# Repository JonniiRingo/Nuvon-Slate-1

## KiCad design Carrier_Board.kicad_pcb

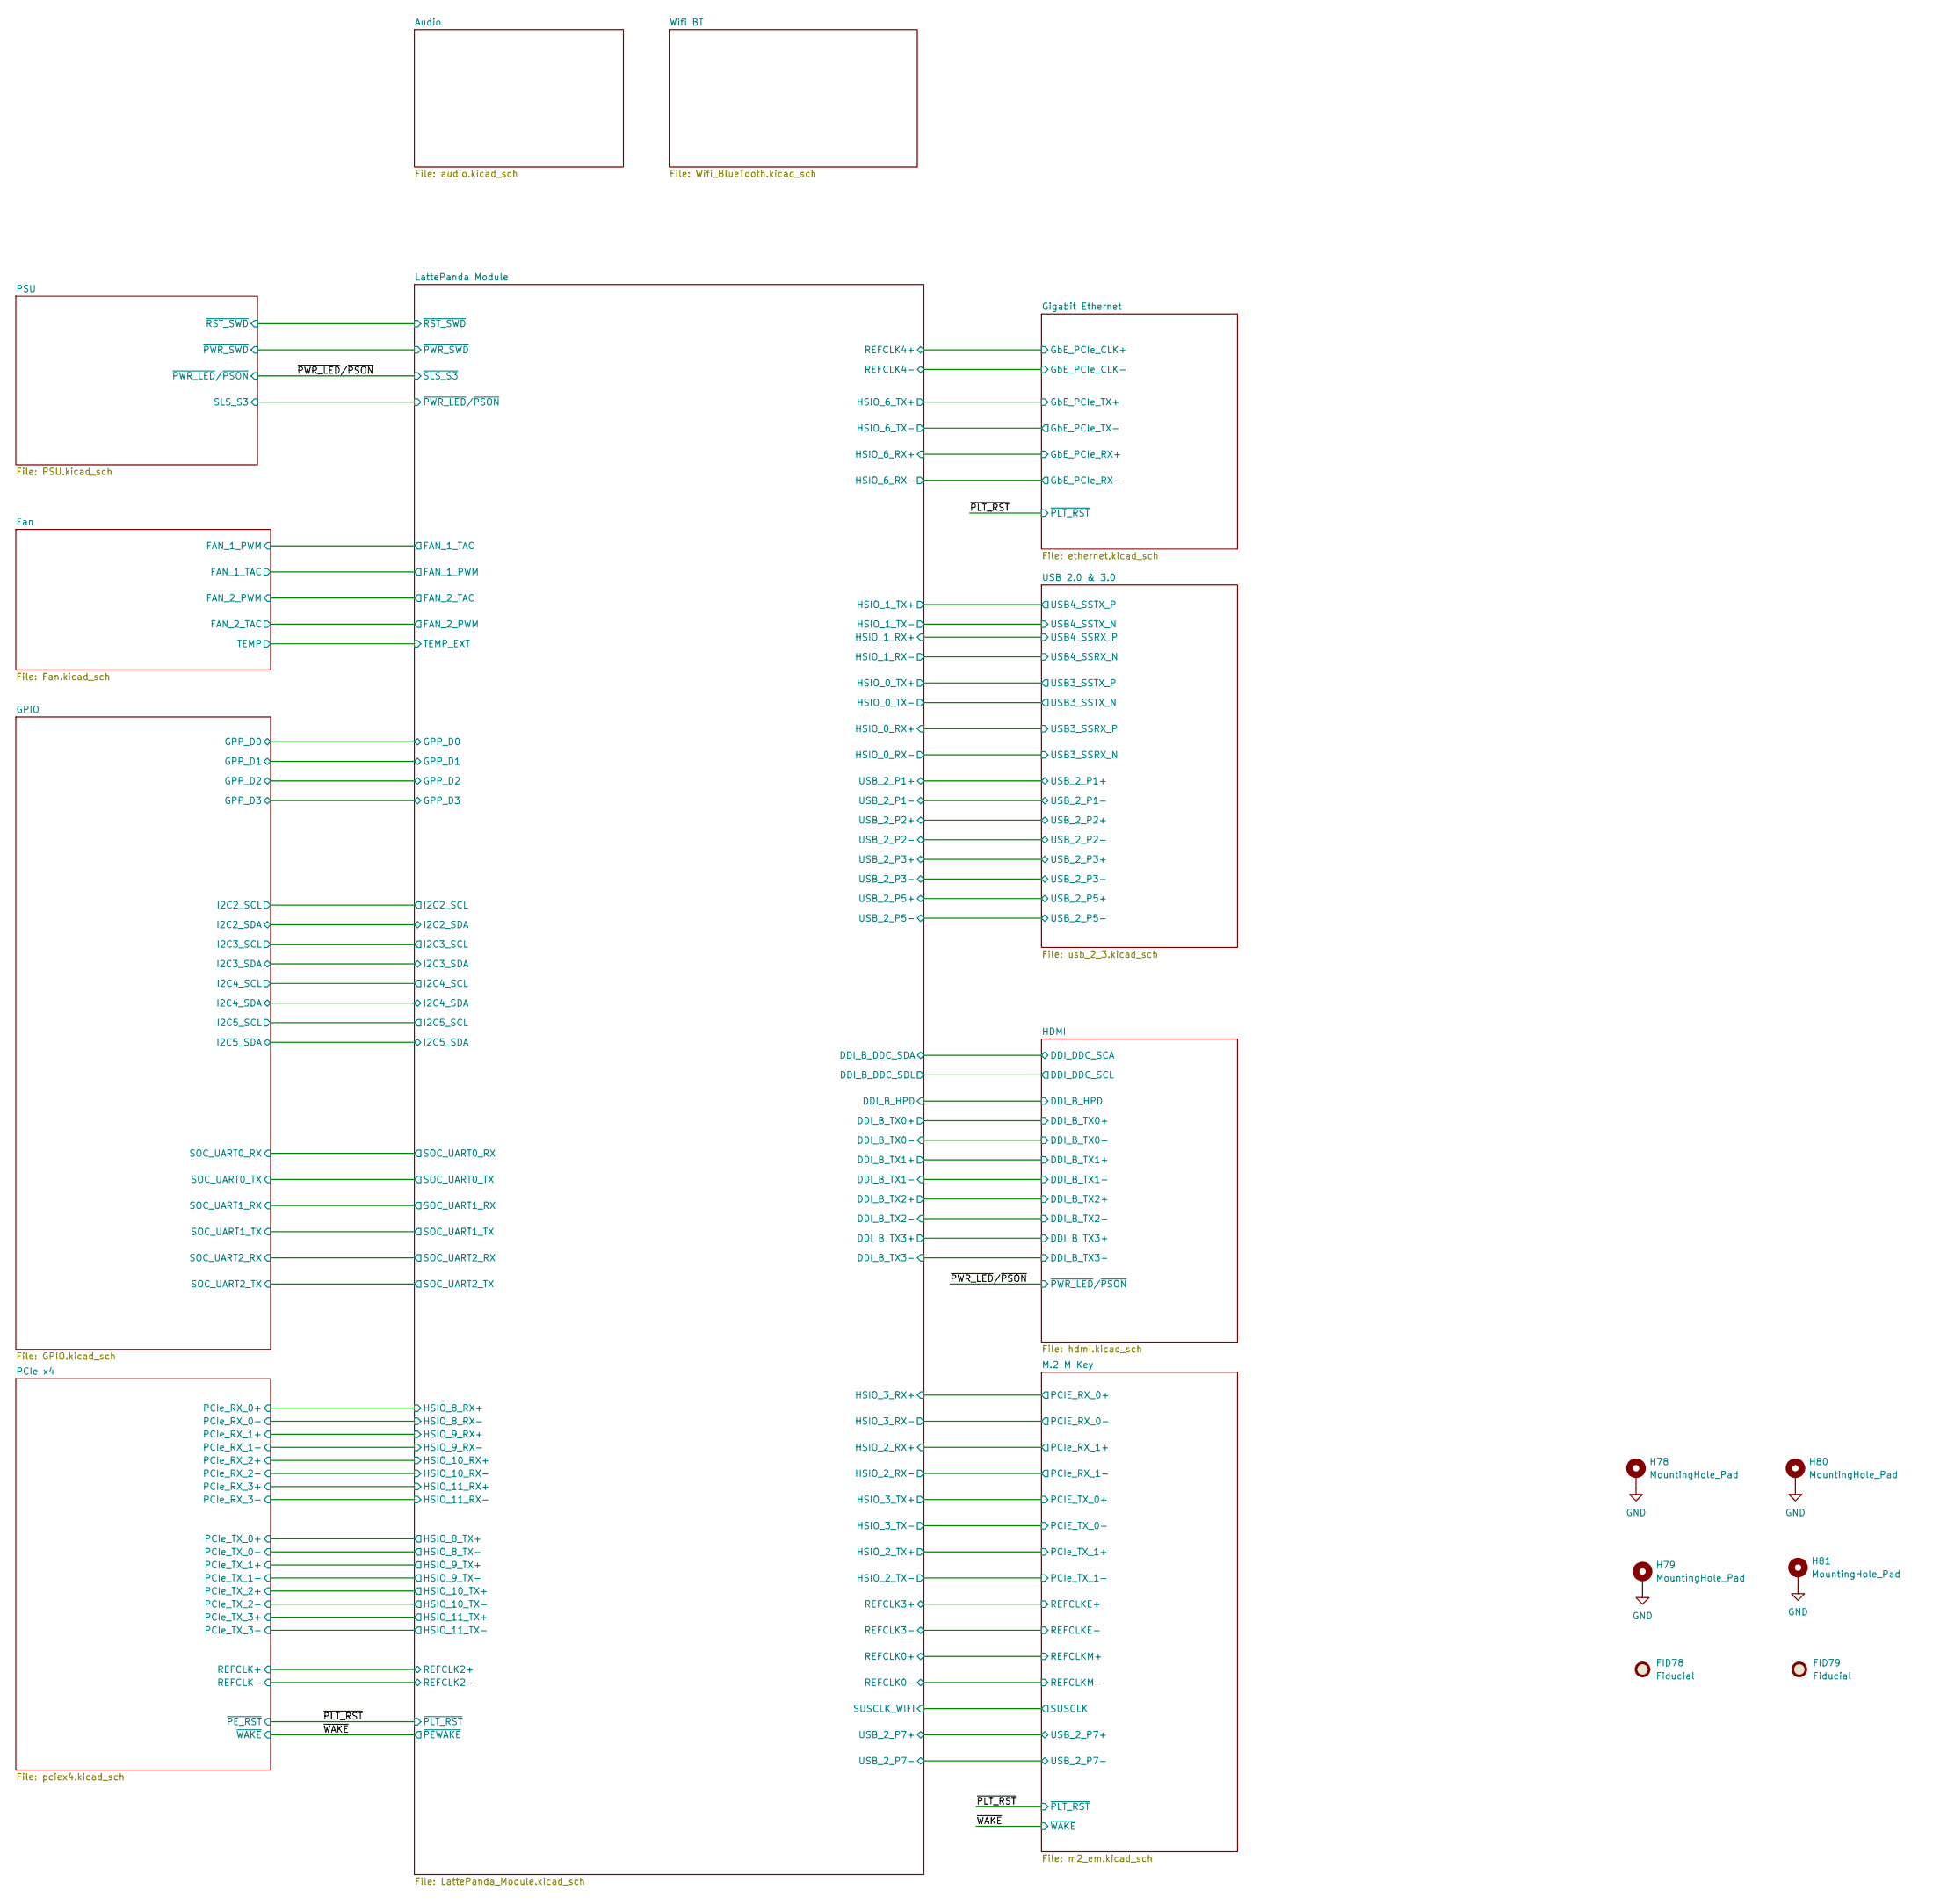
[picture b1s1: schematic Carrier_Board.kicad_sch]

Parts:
FID78, FID79: Fiducial; Fiducial_0.5mm_Mask1mm
H78, H79, H80, H81: MountingHole_Pad; MountingHole_3.2mm_M3_Pad_Via

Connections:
GND: H78.1 (1_1), H79.1 (1_1), H80.1 (1_1), H81.1 (1_1); also elsewhere on the board

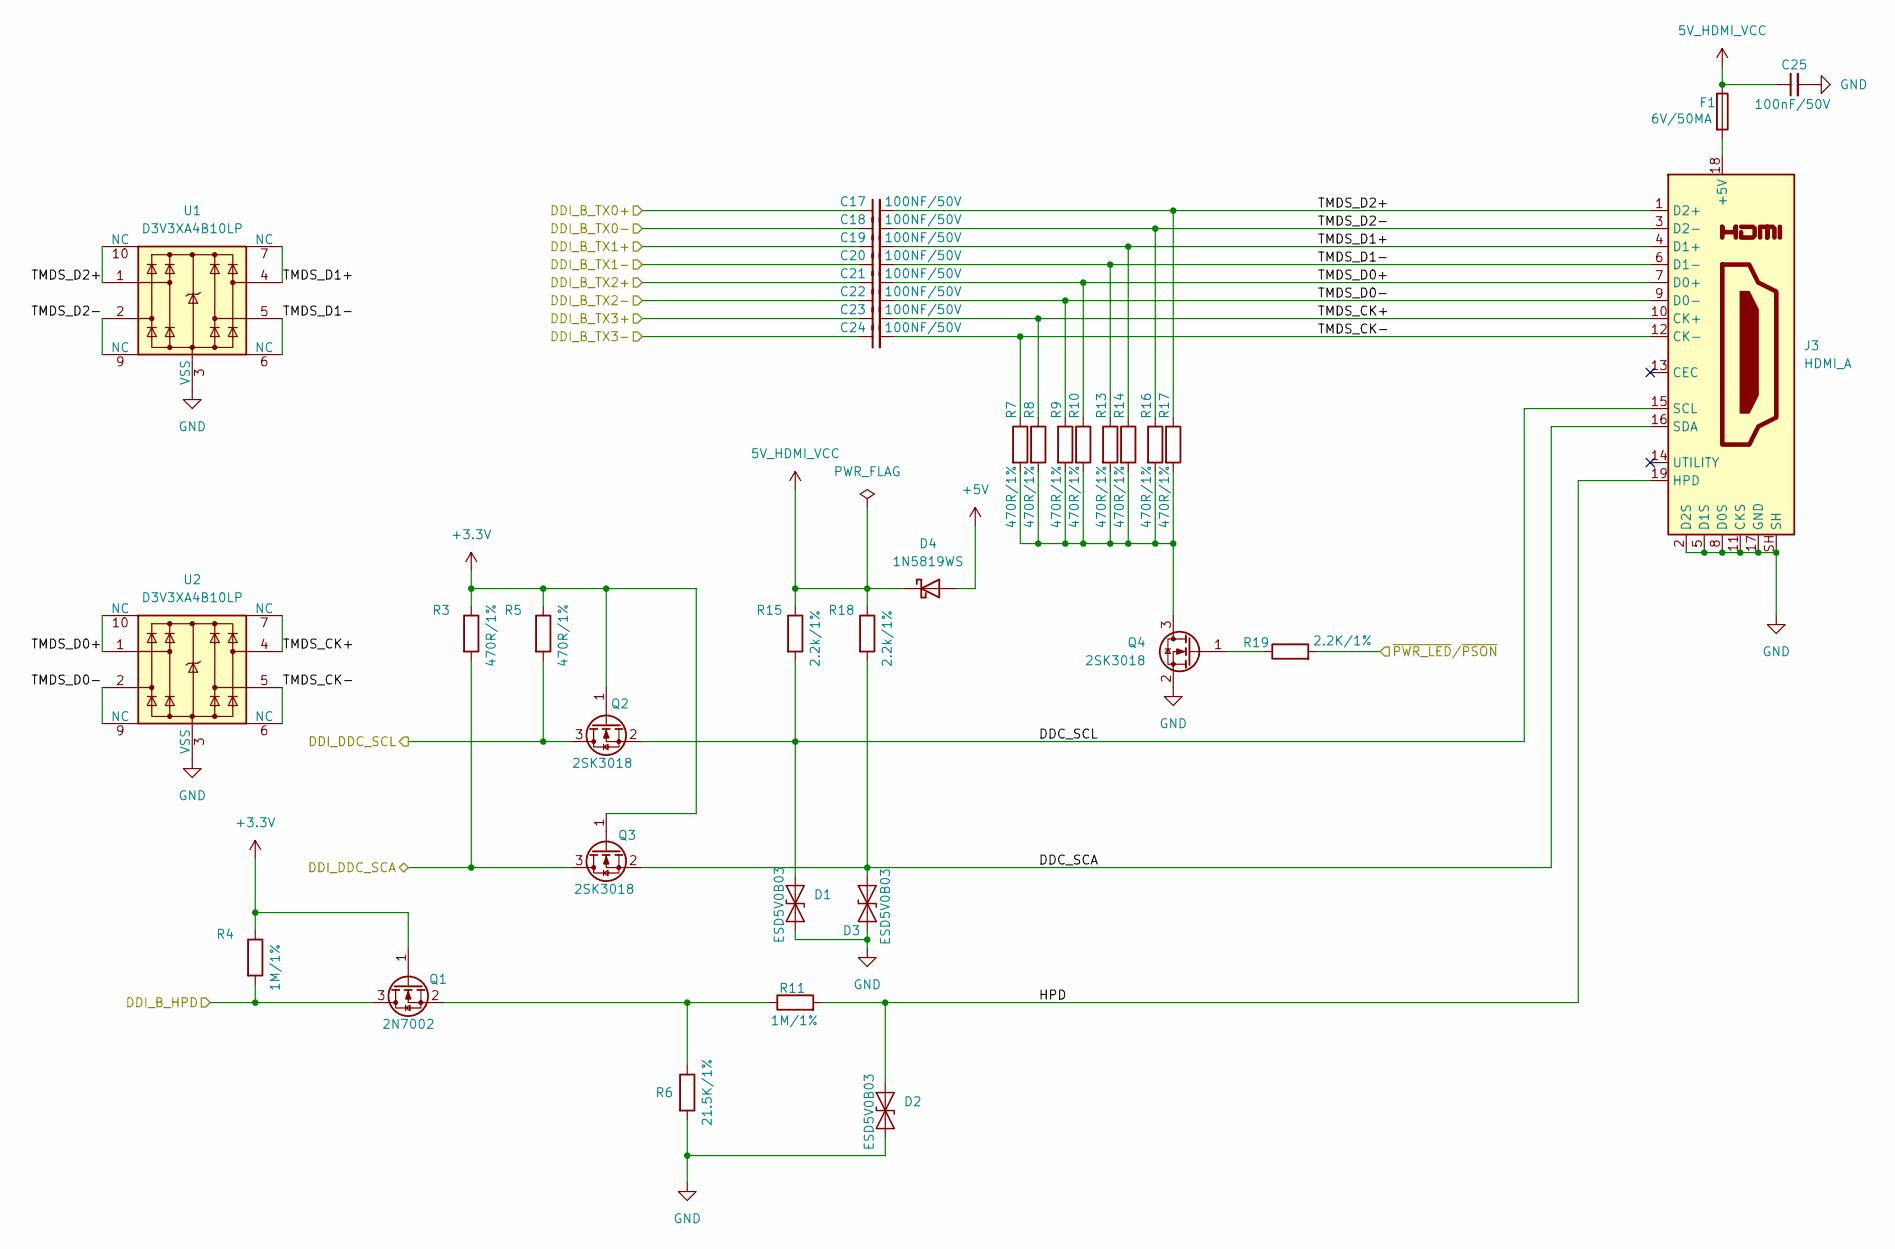
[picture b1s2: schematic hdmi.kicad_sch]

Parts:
C17, C18, C19, C20, C21, C22, C23, C24: 100NF/50V; C_0402_1005Metric
C25: 100nF/50V; C_0402_1005Metric
D1, D2, D3: ESD5V0B03; D_0402_1005Metric
D4: 1N5819WS; D_SOD-323
F1: 6V/50MA; C_0603_1608Metric
J3: HDMI_A; HDMI_A_Molex_208658-1001_Horizontal
Q1: 2N7002; SOT-23
Q2, Q3, Q4: 2SK3018; SOT-23
R3, R5, R7, R8, R9, R10, R13, R14, R16, R17: 470R/1%; R_0402_1005Metric
R4, R11: 1M/1%; R_0402_1005Metric
R6: 21.5K/1%; R_0402_1005Metric
R15, R18: 2.2k/1%; R_0402_1005Metric
R19: 2.2K/1%; R_0402_1005Metric
U1, U2: D3V3XA4B10LP; Diodes_UDFN-10_1.0x2.5mm_P0.5mm

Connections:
5V_HDMI_VCC: C25.1, D4.1 (K), F1.1, R15.1, R18.1
+3.3V: Q1.1 (G), Q2.1 (G), Q3.1 (G), R3.1, R4.1, R5.1; also elsewhere on the board
+5V: D4.2 (A); also elsewhere on the board
/HDMI/DDC_SCA: D3.2 (A2), J3.16 (SDA), Q3.2 (S), R18.2
/HDMI/DDC_SCL: D1.2 (A2), J3.15 (SCL), Q2.2 (S), R15.2
/HDMI/DDI_B_HPD: Q1.3 (D), R4.2; also elsewhere on the board
/HDMI/DDI_B_TX0+: C17.1; also elsewhere on the board
/HDMI/DDI_B_TX0-: C18.1; also elsewhere on the board
/HDMI/DDI_B_TX1+: C19.1; also elsewhere on the board
/HDMI/DDI_B_TX1-: C20.1; also elsewhere on the board
/HDMI/DDI_B_TX2+: C21.1; also elsewhere on the board
/HDMI/DDI_B_TX2-: C22.1; also elsewhere on the board
/HDMI/DDI_B_TX3+: C23.1; also elsewhere on the board
/HDMI/DDI_B_TX3-: C24.1; also elsewhere on the board
/HDMI/DDI_DDC_SCA: Q3.3 (D), R3.2; also elsewhere on the board
/HDMI/DDI_DDC_SCL: Q2.3 (D), R5.2; also elsewhere on the board
/HDMI/HPD: D2.2 (A2), J3.19 (HPD), R11.2
/HDMI/TMDS_CK+: C23.2, J3.10 (CK+), R8.1, U2.4, U2.7 (NC)
/HDMI/TMDS_CK-: C24.2, J3.12 (CK-), R7.1, U2.5, U2.6 (NC)
/HDMI/TMDS_D0+: C21.2, J3.7 (D0+), R10.1, U2.1, U2.10 (NC)
/HDMI/TMDS_D0-: C22.2, J3.9 (D0-), R9.1, U2.2, U2.9 (NC)
/HDMI/TMDS_D1+: C19.2, J3.4 (D1+), R14.1, U1.4, U1.7 (NC)
/HDMI/TMDS_D1-: C20.2, J3.6 (D1-), R13.1, U1.5, U1.6 (NC)
/HDMI/TMDS_D2+: C17.2, J3.1 (D2+), R17.1, U1.1, U1.10 (NC)
/HDMI/TMDS_D2-: C18.2, J3.3 (D2-), R16.1, U1.2, U1.9 (NC)
/~PWR_LED/~PSON: R19.2; also elsewhere on the board
GND: C25.2, D1.1 (A1), D2.1 (A1), D3.1 (A1), J3.2 (D2S), J3.5 (D1S), J3.8 (D0S), J3.11 (CKS), J3.17 (GND), J3.SH, Q4.2 (S), R6.2, U1.3 (VSS), U1.8 (VSS), U2.3 (VSS), U2.8 (VSS); also elsewhere on the board
unnamed: F1.2, J3.18 (+5V)
unnamed: Q1.2 (S), R6.1, R11.1
unnamed: Q4.3 (D), R7.2, R8.2, R9.2, R10.2, R13.2, R14.2, R16.2, R17.2
unnamed: Q4.1 (G), R19.1

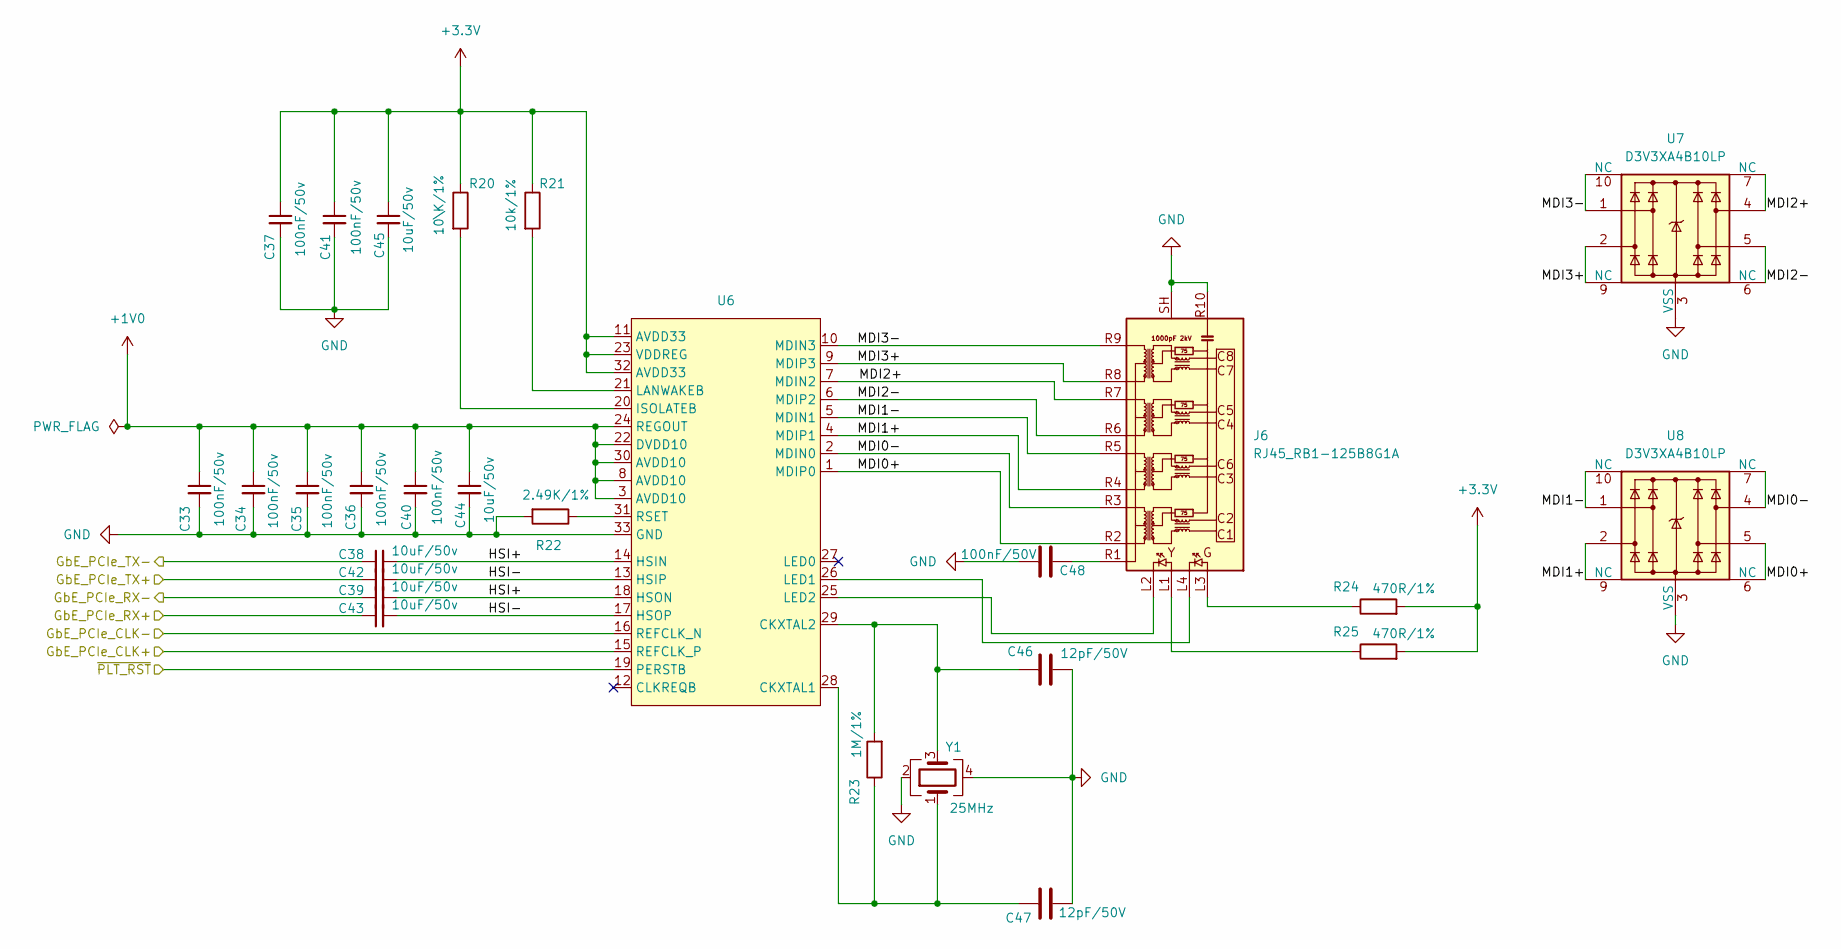
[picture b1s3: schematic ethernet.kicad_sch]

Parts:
C33, C34, C35, C36, C37, C40, C41: 100nF/50v; C_0402_1005Metric
C38, C39, C42, C43, C44, C45: 10uF/50v; C_0402_1005Metric
C46, C47: 12pF/50V; C_0402_1005Metric
C48: 100nF/50V; C_0402_1005Metric
J6: RJ45_RB1-125B8G1A; RJ45_UDE_RB1-125B8G1A
R20: 10\K/1%; R_0603_1608Metric
R21: 10k/1%; R_0603_1608Metric
R22: 2.49K/1%; R_0603_1608Metric
R23: 1M/1%; R_0402_1005Metric
R24, R25: 470R/1%; R_0402_1005Metric
U6: RTL8111H-CG-RH; QFN-32-1EP_4x4mm_P0.4mm_EP2.65x2.65mm
U7, U8: D3V3XA4B10LP; Diodes_UDFN-10_1x2.5mm_P0.5mm
Y1: 25MHz; Crystal_SMD_3225-4Pin_3.2x2.5mm

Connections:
+1V0: C33.1, C34.1, C35.1, C36.1, C40.1, C44.1, U6.3 (AVDD10), U6.8 (AVDD10), U6.22 (DVDD10), U6.24 (REGOUT), U6.30 (AVDD10)
+3.3V: C37.1, C41.1, C45.1, R20.1, R21.1, R24.2, R25.2, U6.11 (AVDD33), U6.23 (VDDREG), U6.32 (AVDD33); also elsewhere on the board
/Gigabit Ethernet/GbE_PCIe_CLK+: U6.15 (REFCLK_P); also elsewhere on the board
/Gigabit Ethernet/GbE_PCIe_CLK-: U6.16 (REFCLK_N); also elsewhere on the board
/Gigabit Ethernet/GbE_PCIe_RX+: C43.1; also elsewhere on the board
/Gigabit Ethernet/GbE_PCIe_RX-: C39.1; also elsewhere on the board
/Gigabit Ethernet/GbE_PCIe_TX+: C42.1; also elsewhere on the board
/Gigabit Ethernet/GbE_PCIe_TX-: C38.1; also elsewhere on the board
/Gigabit Ethernet/HSI+: C38.2, C39.2, U6.14 (HSIN), U6.18 (HSON)
/Gigabit Ethernet/HSI-: C42.2, C43.2, U6.13 (HSIP), U6.17 (HSOP)
/Gigabit Ethernet/MDI0+: J6.R2 (TD1+), U6.1 (MDIP0), U8.5, U8.6 (NC)
/Gigabit Ethernet/MDI0-: J6.R3 (TD1-), U6.2 (MDIN0), U8.4, U8.7 (NC)
/Gigabit Ethernet/MDI1+: J6.R4 (TD2+), U6.4 (MDIP1), U8.2, U8.9 (NC)
/Gigabit Ethernet/MDI1-: J6.R5 (TD2-), U6.5 (MDIN1), U8.1, U8.10 (NC)
/Gigabit Ethernet/MDI2+: J6.R7 (TD3-), U6.7 (MDIN2), U7.4, U7.7 (NC)
/Gigabit Ethernet/MDI2-: J6.R6 (TD3+), U6.6 (MDIP2), U7.5, U7.6 (NC)
/Gigabit Ethernet/MDI3+: J6.R8 (TD4+), U6.9 (MDIP3), U7.2, U7.9 (NC)
/Gigabit Ethernet/MDI3-: J6.R9 (TD4-), U6.10 (MDIN3), U7.1, U7.10 (NC)
/~PLT_RST: U6.19 (PERSTB); also elsewhere on the board
GND: C33.2, C34.2, C35.2, C36.2, C37.2, C40.2, C41.2, C44.2, C45.2, C46.2, C47.2, C48.1, J6.R10 (GND), J6.SH, R22.2, U6.33 (GND), U7.3 (VSS), U7.8 (VSS), U8.3 (VSS), U8.8 (VSS), Y1.2 (G), Y1.4 (G); also elsewhere on the board
unnamed: C48.2, J6.R1 (CT)
unnamed: J6.L1, R25.1
unnamed: J6.L3, R24.1
unnamed: C47.1, R23.1, U6.28 (CKXTAL1), Y1.1
unnamed: C46.1, R23.2, U6.29 (CKXTAL2), Y1.3
unnamed: R20.2, U6.20 (ISOLATEB)
unnamed: R21.2, U6.21 (LANWAKEB)
unnamed: J6.L4, U6.26 (LED1)
unnamed: J6.L2, U6.25 (LED2)
unnamed: R22.1, U6.31 (RSET)

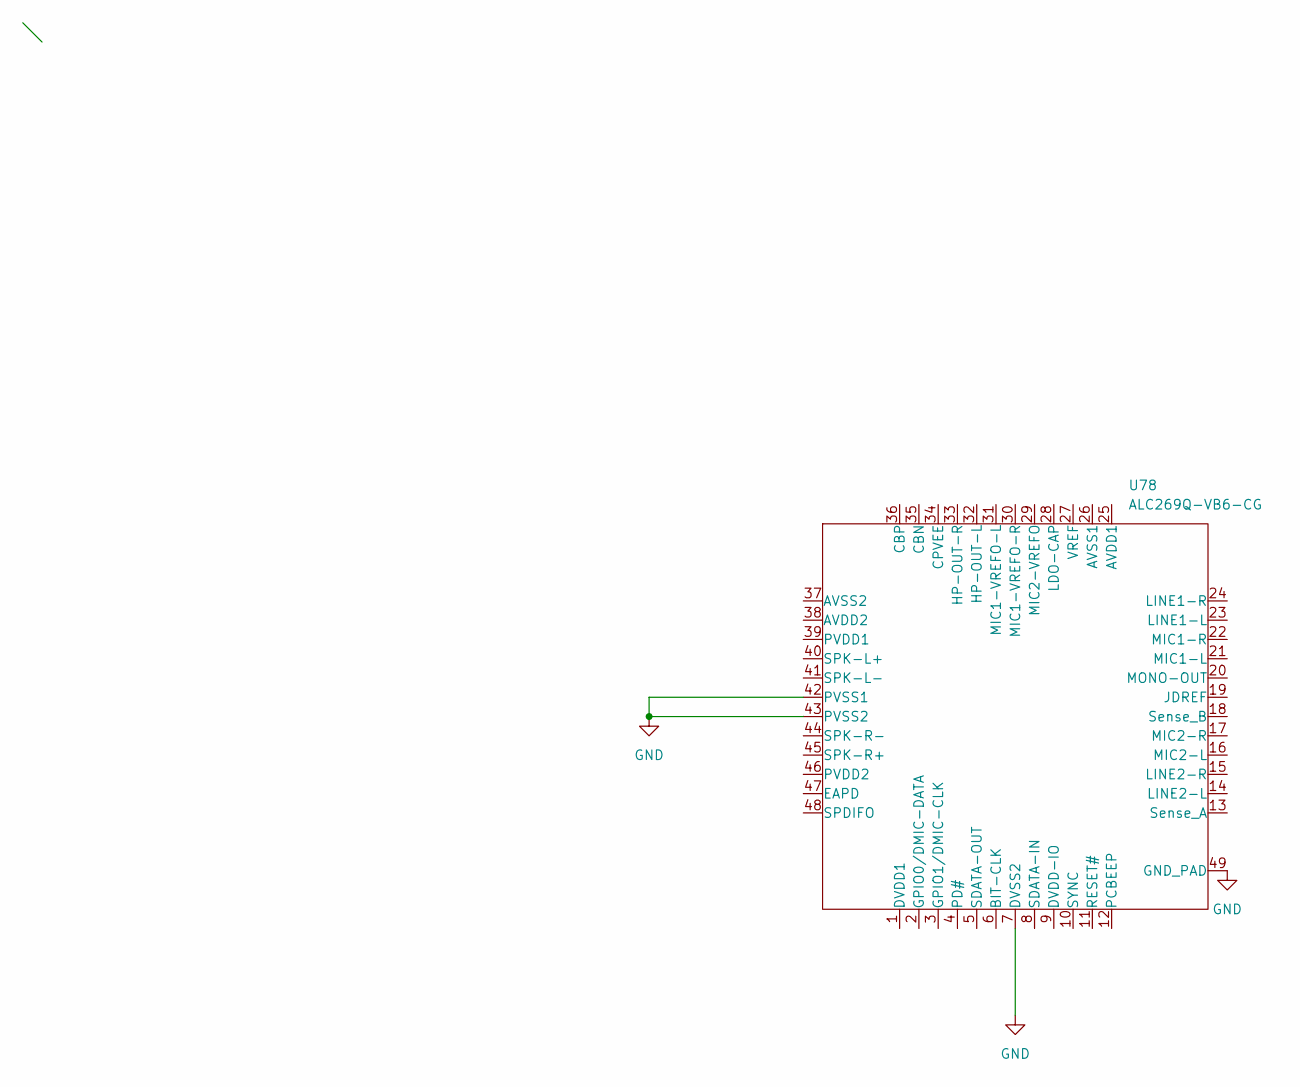
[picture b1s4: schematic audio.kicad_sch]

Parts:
U78: ALC269Q-VB6-CG; QFN-48-1EP_7x7mm_P0.5mm_EP5.15x5.15mm

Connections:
GND: U78.7 (DVSS2), U78.42 (PVSS1), U78.43 (PVSS2), U78.49 (GND_PAD); also elsewhere on the board
